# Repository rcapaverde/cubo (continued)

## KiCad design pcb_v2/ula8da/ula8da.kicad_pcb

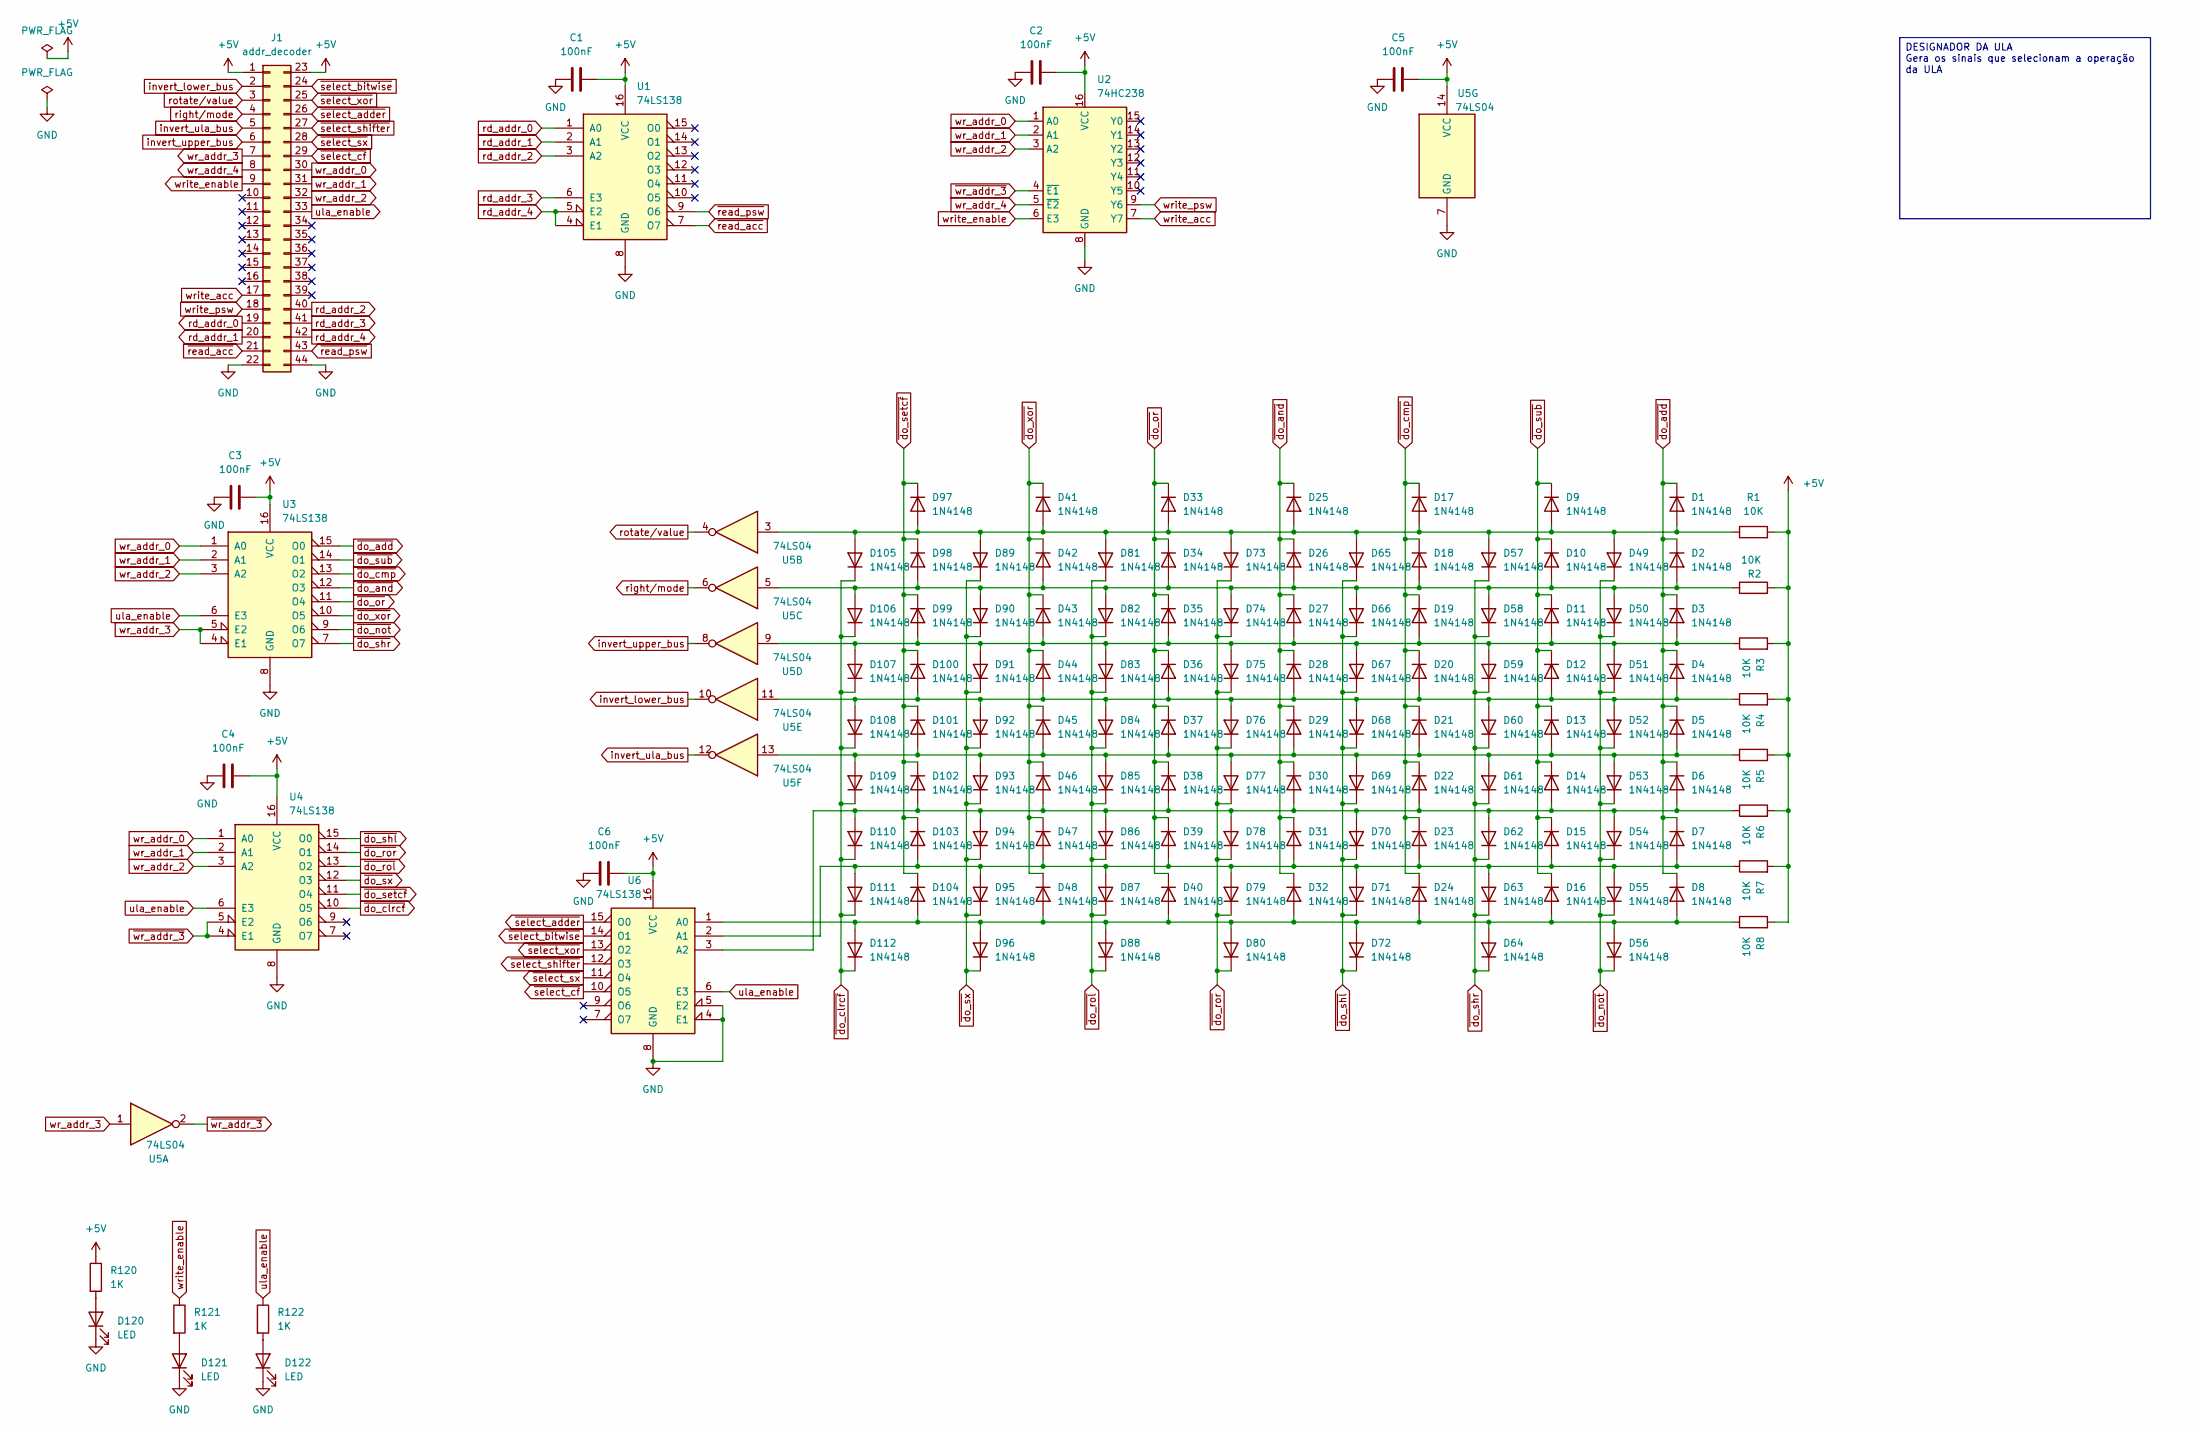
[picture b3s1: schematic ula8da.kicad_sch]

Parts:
C1, C2, C3, C4, C5, C6: 100nF; C_Disc_D5.1mm_W3.2mm_P5.00mm
D1, D2, D3, D4, D5, D6, D7, D8, D9, D10, D11, D12, D13, D14, D15, D16, D17, D18, D19, D20, D21, D22, D23, D24, D25, D26, D27, D28, D29, D30, D31, D32, D33, D34, D35, D36, D37, D38, D39, D40, D41, D42, D43, D44, D45, D46, D47, D48, D49, D50, D51, D52, D53, D54, D55, D56, D57, D58, D59, D60, D61, D62, D63, D64, D65, D66, D67, D68, D69, D70, D71, D72, D73, D74, D75, D76, D77, D78, D79, D80, D81, D82, D83, D84, D85, D86, D87, D88, D89, D90, D91, D92, D93, D94, D95, D96, D97, D98, D99, D100, D101, D102, D103, D104, D105, D106, D107, D108, D109, D110, D111, D112: 1N4148; D_DO-35_SOD27_P3.81mm_Vertical_KathodeUp
D120, D121, D122: LED; LED_D5.0mm
J1: addr_decoder; edge-connector-44
R1, R2, R3, R4, R5, R6, R7, R8: 10K; R_Axial_DIN0207_L6.3mm_D2.5mm_P7.62mm_Horizontal
R120, R121, R122: 1K; R_Axial_DIN0207_L6.3mm_D2.5mm_P7.62mm_Horizontal
U1, U3, U4, U6: 74LS138; DIP-16_W7.62mm
U2: 74HC238; DIP-16_W7.62mm
U5: 74LS04; DIP-14_W7.62mm

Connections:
+5V: C1.2, C2.2, C3.2, C4.2, C5.2, C6.2, J1.1, J1.23, R1.2, R2.2, R3.2, R4.2, R5.2, R6.2, R7.2, R8.2, R120.1, U1.16 (VCC), U2.16 (VCC), U3.16 (VCC), U4.16 (VCC), U5.14 (VCC), U6.16 (VCC)
GND: C1.1, C2.1, C3.1, C4.1, C5.1, C6.1, D120.1 (K), D121.1 (K), D122.1 (K), J1.22, J1.44, U1.8 (GND), U2.8 (GND), U3.8 (GND), U4.8 (GND), U5.7 (GND), U6.4 (E1), U6.5 (E2), U6.8 (GND)
unnamed: D1.2 (A), D9.2 (A), D17.2 (A), D25.2 (A), D33.2 (A), D41.2 (A), D49.2 (A), D57.2 (A), D65.2 (A), D73.2 (A), D81.2 (A), D89.2 (A), D97.2 (A), D105.2 (A), R1.1, U5.3
unnamed: D2.2 (A), D10.2 (A), D18.2 (A), D26.2 (A), D34.2 (A), D42.2 (A), D50.2 (A), D58.2 (A), D66.2 (A), D74.2 (A), D82.2 (A), D90.2 (A), D98.2 (A), D106.2 (A), R2.1, U5.5
unnamed: D4.2 (A), D12.2 (A), D20.2 (A), D28.2 (A), D36.2 (A), D44.2 (A), D52.2 (A), D60.2 (A), D68.2 (A), D76.2 (A), D84.2 (A), D92.2 (A), D100.2 (A), D108.2 (A), R4.1, U5.11
unnamed: D5.2 (A), D13.2 (A), D21.2 (A), D29.2 (A), D37.2 (A), D45.2 (A), D53.2 (A), D61.2 (A), D69.2 (A), D77.2 (A), D85.2 (A), D93.2 (A), D101.2 (A), D109.2 (A), R5.1, U5.13
unnamed: D6.2 (A), D14.2 (A), D22.2 (A), D30.2 (A), D38.2 (A), D46.2 (A), D54.2 (A), D62.2 (A), D70.2 (A), D78.2 (A), D86.2 (A), D94.2 (A), D102.2 (A), D110.2 (A), R6.1, U6.3 (A2)
unnamed: D7.2 (A), D15.2 (A), D23.2 (A), D31.2 (A), D39.2 (A), D47.2 (A), D55.2 (A), D63.2 (A), D71.2 (A), D79.2 (A), D87.2 (A), D95.2 (A), D103.2 (A), D111.2 (A), R7.1, U6.2 (A1)
unnamed: D8.2 (A), D16.2 (A), D24.2 (A), D32.2 (A), D40.2 (A), D48.2 (A), D56.2 (A), D64.2 (A), D72.2 (A), D80.2 (A), D88.2 (A), D96.2 (A), D104.2 (A), D112.2 (A), R8.1, U6.1 (A0)
unnamed: D3.2 (A), D11.2 (A), D19.2 (A), D27.2 (A), D35.2 (A), D43.2 (A), D51.2 (A), D59.2 (A), D67.2 (A), D75.2 (A), D83.2 (A), D91.2 (A), D99.2 (A), D107.2 (A), R3.1, U5.9
unnamed: D120.2 (A), R120.2
unnamed: D121.2 (A), R121.2
unnamed: D122.2 (A), R122.2
invert_lower_bus: J1.2, U5.10
invert_ula_bus: J1.5, U5.12
invert_upper_bus: J1.6, U5.8
rd_addr_0: J1.19, U1.1 (A0)
rd_addr_1: J1.20, U1.2 (A1)
rd_addr_2: J1.40, U1.3 (A2)
rd_addr_3: J1.41, U1.6 (E3)
rd_addr_4: J1.42, U1.4 (E1), U1.5 (E2)
right/mode: J1.4, U5.6
rotate/value: J1.3, U5.4
ula_enable: J1.33, R122.1, U3.6 (E3), U4.6 (E3), U6.6 (E3)
wr_addr_0: J1.30, U2.1 (A0), U3.1 (A0), U4.1 (A0)
wr_addr_1: J1.31, U2.2 (A1), U3.2 (A1), U4.2 (A1)
wr_addr_2: J1.32, U2.3 (A2), U3.3 (A2), U4.3 (A2)
wr_addr_3: J1.7, U3.4 (E1), U3.5 (E2), U5.1
wr_addr_4: J1.8, U2.5 (~E2)
write_acc: J1.17, U2.7 (Y7)
write_enable: J1.9, R121.1, U2.6 (E3)
write_psw: J1.18, U2.9 (Y6)
~do_add: D1.1 (K), D2.1 (K), D3.1 (K), D4.1 (K), D5.1 (K), D6.1 (K), D7.1 (K), D8.1 (K), U3.15 (O0)
~do_and: D25.1 (K), D26.1 (K), D27.1 (K), D28.1 (K), D29.1 (K), D30.1 (K), D31.1 (K), D32.1 (K), U3.12 (O3)
~do_clrcf: D105.1 (K), D106.1 (K), D107.1 (K), D108.1 (K), D109.1 (K), D110.1 (K), D111.1 (K), D112.1 (K), U4.10 (O5)
~do_cmp: D17.1 (K), D18.1 (K), D19.1 (K), D20.1 (K), D21.1 (K), D22.1 (K), D23.1 (K), D24.1 (K), U3.13 (O2)
~do_not: D49.1 (K), D50.1 (K), D51.1 (K), D52.1 (K), D53.1 (K), D54.1 (K), D55.1 (K), D56.1 (K), U3.9 (O6)
~do_or: D33.1 (K), D34.1 (K), D35.1 (K), D36.1 (K), D37.1 (K), D38.1 (K), D39.1 (K), D40.1 (K), U3.11 (O4)
~do_rol: D81.1 (K), D82.1 (K), D83.1 (K), D84.1 (K), D85.1 (K), D86.1 (K), D87.1 (K), D88.1 (K), U4.13 (O2)
~do_ror: D73.1 (K), D74.1 (K), D75.1 (K), D76.1 (K), D77.1 (K), D78.1 (K), D79.1 (K), D80.1 (K), U4.14 (O1)
~do_setcf: D97.1 (K), D98.1 (K), D99.1 (K), D100.1 (K), D101.1 (K), D102.1 (K), D103.1 (K), D104.1 (K), U4.11 (O4)
~do_shl: D65.1 (K), D66.1 (K), D67.1 (K), D68.1 (K), D69.1 (K), D70.1 (K), D71.1 (K), D72.1 (K), U4.15 (O0)
~do_shr: D57.1 (K), D58.1 (K), D59.1 (K), D60.1 (K), D61.1 (K), D62.1 (K), D63.1 (K), D64.1 (K), U3.7 (O7)
~do_sub: D9.1 (K), D10.1 (K), D11.1 (K), D12.1 (K), D13.1 (K), D14.1 (K), D15.1 (K), D16.1 (K), U3.14 (O1)
~do_sx: D89.1 (K), D90.1 (K), D91.1 (K), D92.1 (K), D93.1 (K), D94.1 (K), D95.1 (K), D96.1 (K), U4.12 (O3)
~do_xor: D41.1 (K), D42.1 (K), D43.1 (K), D44.1 (K), D45.1 (K), D46.1 (K), D47.1 (K), D48.1 (K), U3.10 (O5)
~read_acc: J1.21, U1.7 (O7)
~read_psw: J1.43, U1.9 (O6)
~select_adder: J1.26, U6.15 (O0)
~select_bitwise: J1.24, U6.14 (O1)
~select_cf: J1.29, U6.10 (O5)
~select_shifter: J1.27, U6.12 (O3)
~select_sx: J1.28, U6.11 (O4)
~select_xor: J1.25, U6.13 (O2)
~wr_addr_3: U2.4 (~E1), U4.4 (E1), U4.5 (E2), U5.2

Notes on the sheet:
DESIGNADOR DA ULA Gera os sinais que selecionam a operação da ULA

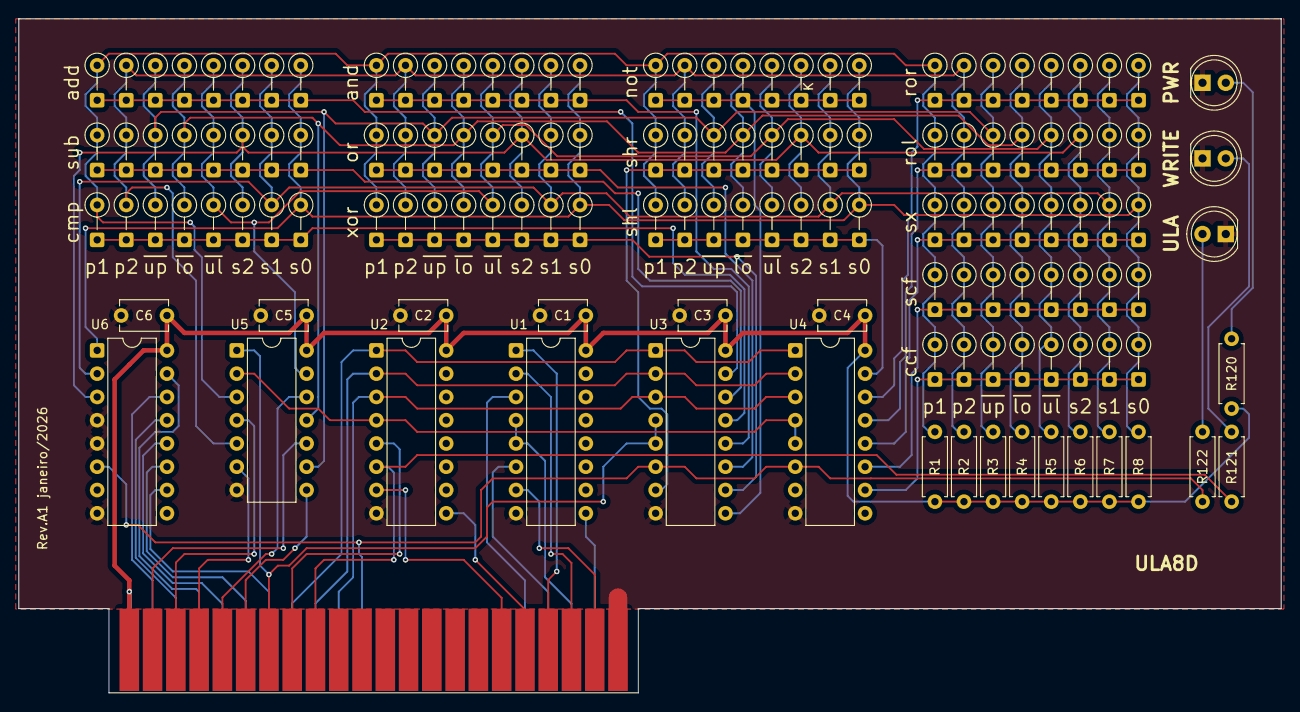
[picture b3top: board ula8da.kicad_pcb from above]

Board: 2 copper layers, 137.8 x 73.6 mm, 139 parts (0 on the bottom side), 55 nets.
